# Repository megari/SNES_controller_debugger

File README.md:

SNES controller debugger
========================

This is a little project for debugging SNES controllers. The PCB design files
and the firmware source code are included.

The hardware uses an Atmel mega32u4 microcontroller.

The firmware uses the [YAAL](https://github.com/raphendyr/yaal) library and
[yaamake](https://github.com/raphendyr/yaamake). These are included as
submodules in the firmware/vendor directory.

Compilation of the firmware
---------------------------

The avr-gcc toolchain is required in order to compile the firmware. The
repositories of your distribution probably have this available.

After the toolchain has been installed:
```sh
cd firmware
```

If you haven't built yaamake yet, do so:
```sh
cd vendor/yaamake
make
cd ../..
```

Finally, build the firmware and program the board:
```sh
nano Makefile # Check that the programmer port is correct
make
make program
```

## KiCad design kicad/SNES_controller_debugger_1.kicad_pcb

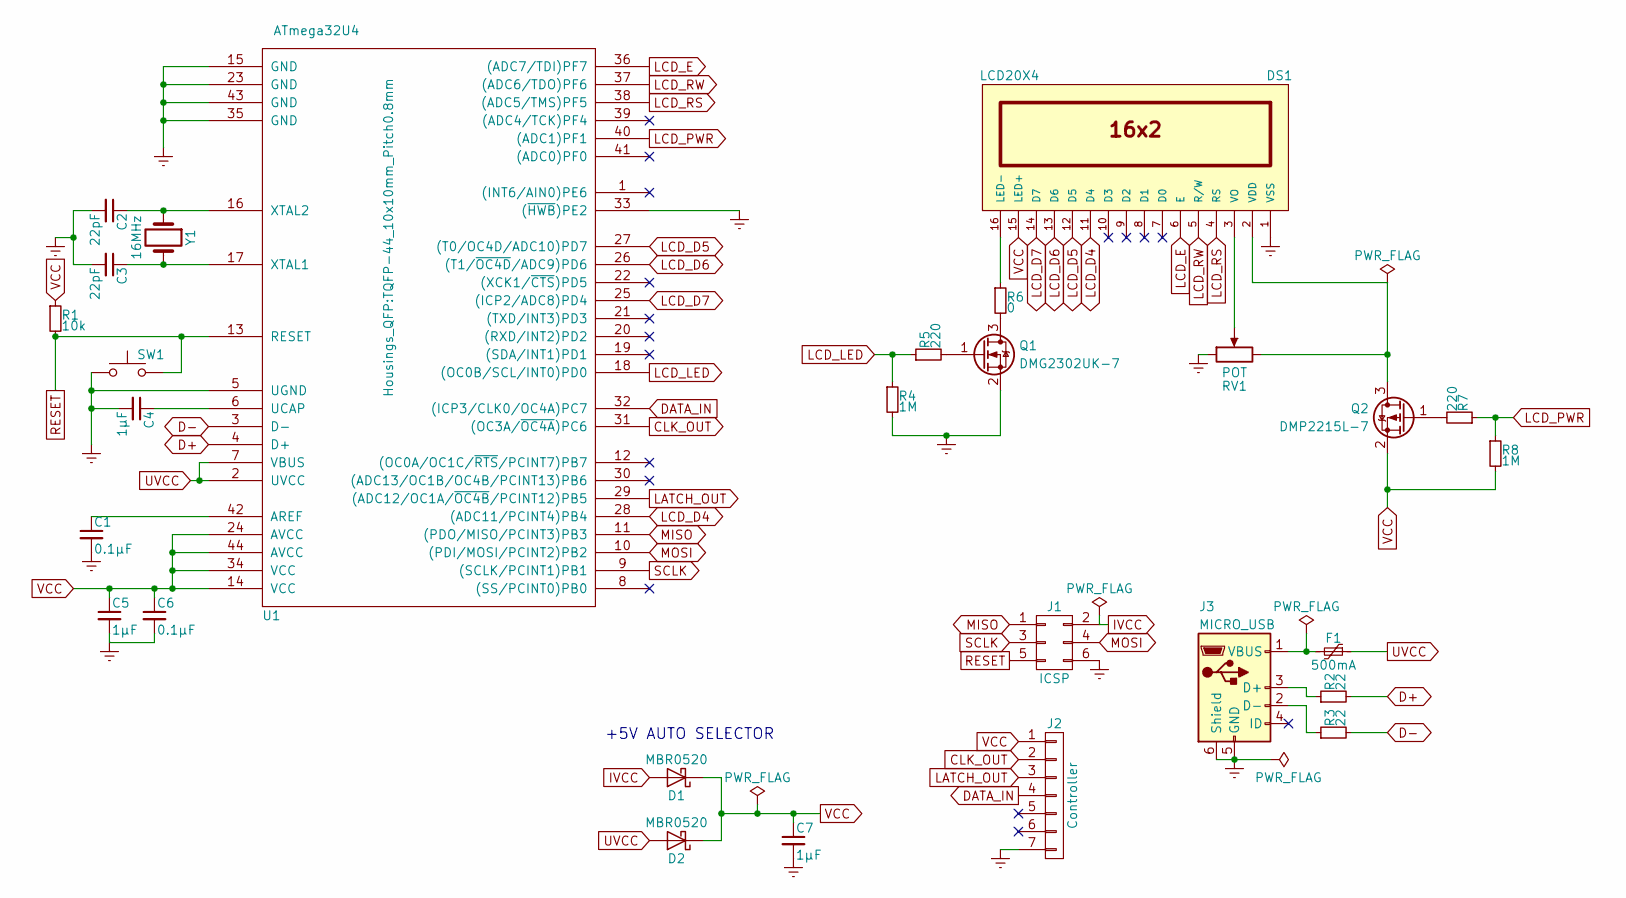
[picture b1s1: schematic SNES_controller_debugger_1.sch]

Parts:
C1, C6: 0.1µF; C_0603_HandSoldering
C2, C3: 22pF; C_0603_HandSoldering
C4, C5, C7: 1µF; C_0603_HandSoldering
D1, D2: MBR0520; D_SOD-123
DS1: LCD20X4; LCD_2004_Pitch2.54mm
F1: 500mA; R_0603_HandSoldering
J1: ICSP; Pin_Header_Straight_2x03_Pitch2.54mm
J2: Controller; SNES_controller_port
J3: MICRO_USB; Conn_USBmicro-B_Amphenol_10118194-0001LF; MPN 10118194-0001LF; Digi-Key part number 609-4618-1-ND
Q1: DMG2302UK-7; SOT-23_Handsoldering
Q2: DMP2215L-7; SOT-23_Handsoldering
R1: 10k; R_0603_HandSoldering
R2, R3: 22; R_0805_HandSoldering
R4, R8: 1M; R_0603_HandSoldering
R5, R7: 220; R_0603_HandSoldering
R6: 0; R_0603_HandSoldering
RV1: POT; Potentiometer_Trimmer_Vishay_TS53YL; MPN TS53YL103MR10; Digi-Key part number TS53YL-10KCT-ND
SW1: Reset; SW_PUSH_6mm; MPN MJTP1230; Digi-Key part number 679-2428-ND
U1: ATmega32U4; TQFP-44_10x10mm_Pitch0.8mm; MPN ATMEGA32U4-AU; Digi-Key part number ATMEGA32U4-AU-ND
Y1: 16MHz; Crystal_SMD_5032-2pin_5.0x3.2mm_HandSoldering; MPN NX5032GA-16MHZ-STD-CSK-4; Digi-Key part number 644-1187-1-ND

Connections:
CLK_OUT: J2.2, U1.31 ((OC3A/~OC4A~)PC6)
D+: R2.2, U1.4 (D+)
D-: R3.2, U1.3 (D-)
DATA_IN: J2.4, U1.32 ((ICP3/CLK0/OC4A)PC7)
Earth: C1.2, C2.2, C3.2, C4.2, C5.2, C6.2, C7.2, DS1.1 (VSS), J1.6, J2.7, J3.5 (GND), J3.6 (Shield), Q1.2 (S), R4.2, RV1.1, SW1.1, U1.5 (UGND), U1.15 (GND), U1.23 (GND), U1.33 ((~HWB~)PE2), U1.35 (GND), U1.43 (GND)
IVCC: D1.2 (A), J1.2
LATCH_OUT: J2.3, U1.29 ((ADC12/OC1A/~OC4B~/PCINT12)PB5)
LCD_D4: DS1.11 (D4), U1.28 ((ADC11/PCINT4)PB4)
LCD_D5: DS1.12 (D5), U1.27 ((T0/OC4D/ADC10)PD7)
LCD_D6: DS1.13 (D6), U1.26 ((T1/~OC4D~/ADC9)PD6)
LCD_D7: DS1.14 (D7), U1.25 ((ICP2/ADC8)PD4)
LCD_E: DS1.6 (E), U1.36 ((ADC7/TDI)PF7)
LCD_LED: R4.1, R5.1, U1.18 ((OC0B/SCL/INT0)PD0)
LCD_PWR: R7.1, R8.1, U1.40 ((ADC1)PF1)
LCD_RS: DS1.4 (RS), U1.38 ((ADC5/TMS)PF5)
LCD_RW: DS1.5 (R/W), U1.37 ((ADC6/TDO)PF6)
MISO: J1.1, U1.11 ((PDO/MISO/PCINT3)PB3)
MOSI: J1.4, U1.10 ((PDI/MOSI/PCINT2)PB2)
unnamed: C1.1, U1.42 (AREF)
unnamed: C2.1, U1.16 (XTAL2), Y1.1
unnamed: C3.1, U1.17 (XTAL1), Y1.2
unnamed: C4.1, U1.6 (UCAP)
unnamed: DS1.2 (VDD), Q2.3 (D), RV1.3
unnamed: DS1.3 (VO), RV1.2
unnamed: DS1.16 (LED-), R6.1
unnamed: F1.2, J3.1 (VBUS)
unnamed: J3.2 (D-), R3.1
unnamed: J3.3 (D+), R2.1
unnamed: Q1.1 (G), R5.2
unnamed: Q1.3 (D), R6.2
unnamed: Q2.1 (G), R7.2
RESET: J1.5, R1.2, SW1.2, U1.13 (RESET)
SCLK: J1.3, U1.9 ((SCLK/PCINT1)PB1)
UVCC: D2.2 (A), F1.1, U1.2 (UVCC), U1.7 (VBUS)
VCC: C5.1, C6.1, C7.1, D1.1 (K), D2.1 (K), DS1.15 (LED+), J2.1, Q2.2 (S), R1.1, R8.2, U1.14 (VCC), U1.24 (AVCC), U1.34 (VCC), U1.44 (AVCC)

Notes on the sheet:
+5V AUTO SELECTOR

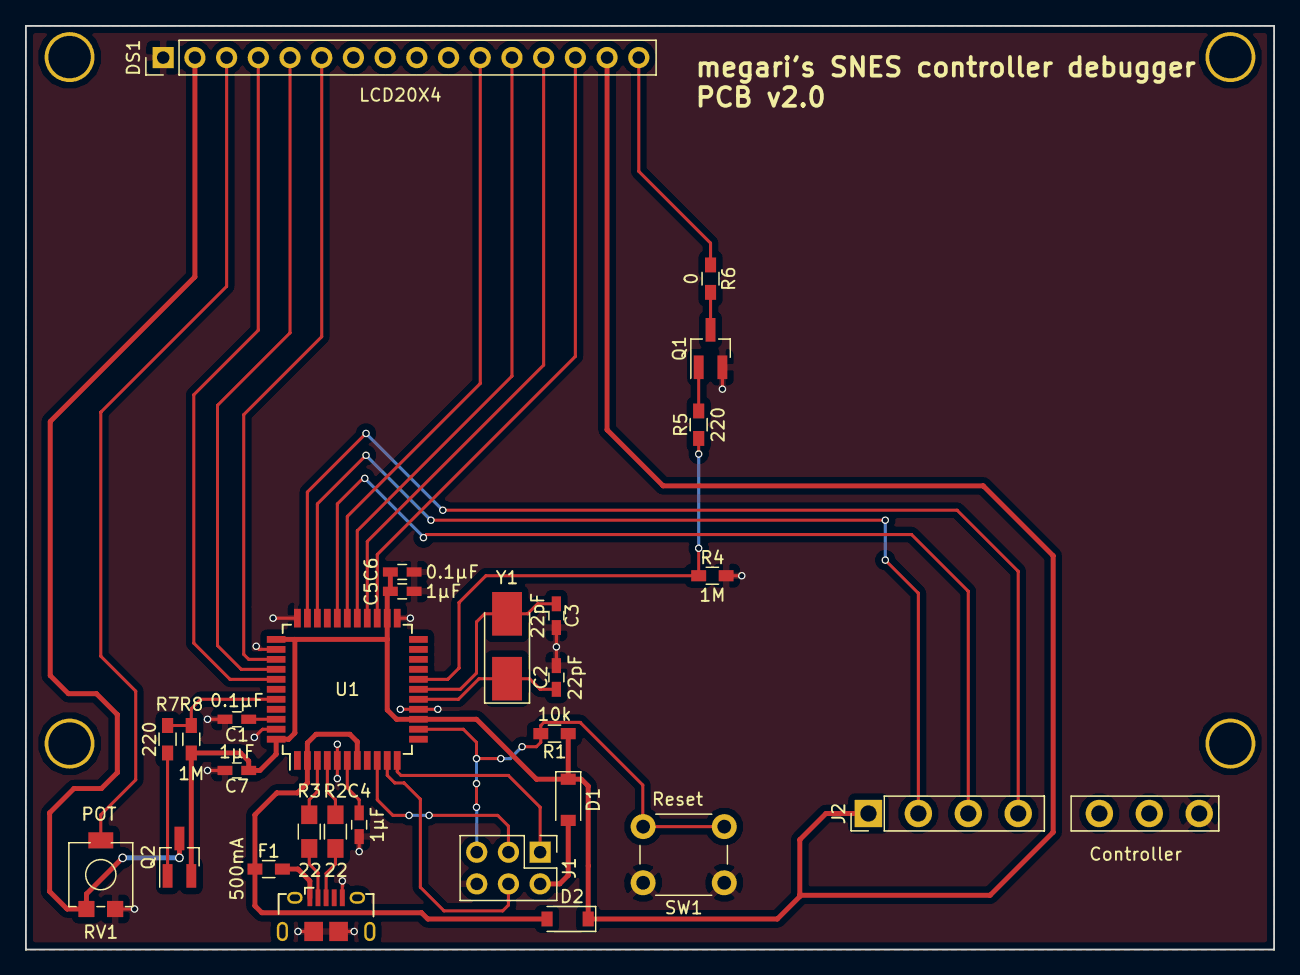
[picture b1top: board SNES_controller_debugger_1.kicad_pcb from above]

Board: 2 copper layers, 100.0 x 74.0 mm, 32 parts (0 on the bottom side), 35 nets.

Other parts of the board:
H1, H2, H3, H4: MountingHole_3.4mm

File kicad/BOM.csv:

"Id";"Designator";"Package";"Quantity";"Designation";"Supplier and ref";
1;"H4,H3,H2,H1";"MountingHole_3.4mm";4;"";;;
2;"U1";"TQFP-44_10x10mm_Pitch0.8mm";1;"ATmega32U4";;;
3;"C1,C6";"C_0603_HandSoldering";2;"0.1µF";;;
4;"C2,C3";"C_0603_HandSoldering";2;"22pF";;;
5;"C4,C5,C7";"C_0603_HandSoldering";3;"1µF";;;
6;"R1";"R_0603_HandSoldering";1;"10k";;;
7;"R2,R3";"R_0805_HandSoldering";2;"22";;;
8;"RV1";"Potentiometer_Trimmer_Vishay_TS53YL";1;"POT";;;
9;"D1,D2";"D_SOD-123";2;"MBR0520";;;
10;"F1";"R_0603_HandSoldering";1;"500mA";;;
11;"SW1";"SW_PUSH_6mm";1;"Reset";;;
12;"Y1";"Crystal_SMD_5032-2pin_5.0x3.2mm_HandSoldering";1;"16MHz";;;
13;"R4,R8";"R_0603_HandSoldering";2;"1M";;;
14;"R5,R7";"R_0603_HandSoldering";2;"220";;;
15;"R6";"R_0603_HandSoldering";1;"0";;;
16;"DS1";"LCD_2004_Pitch2.54mm";1;"LCD20X4";;;
17;"J2";"SNES_controller_port";1;"Controller";;;
18;"J1";"Pin_Header_Straight_2x03_Pitch2.54mm";1;"ICSP";;;
19;"Q1";"SOT-23_Handsoldering";1;"DMG2302UK-7";;;
20;"Q2";"SOT-23_Handsoldering";1;"DMP2215L-7";;;
21;"J3";"Conn_USBmicro-B_Amphenol_10118194-0001LF";1;"MICRO_USB";;;

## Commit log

2017-07-29 firmware: Set yaal submodule origin to upstream repostitory.
2017-08-04 pcb: Tweak USB traces, fill an area with a ground plane.
2017-08-05 pcb: Complete overhaul after getting some advice from an actual electronics engineer.
2017-08-05 pcb: Move C5 and C6 nearer to the MCU.
2017-08-06 pcb: Another complete overhaul under the supervision of Icchan^.
2017-08-07 pcb: Work on reducing the number and length of traces on the back side to make the ground plane more unified.
2017-08-08 pcb: Add Digi-Key part numbers and MPNs to some components
2017-08-10 pcb: Add hardware capability to dim the LCD backlight and to switch power to the LCD
2017-08-10 firmware: Adapt to changes in PCB version 2.0, toggle LCD off and on to re-initialize on reset
2017-08-10 firmware: Turn LCD backlight off after an idle timeout
2017-08-10 pcb: Update the BOM
2017-08-11 pcb: Generate schema PDF
2017-08-14 firmware: Update YAAL
2017-08-15 firmware: Clean up LCD power and backlight control
2017-08-15 pcb, firmware: Using an N-MOSFET to cut power to the LCD from the negative side won't work, so use a P-MOSFET on the positive side
2017-08-21 pcb: Tweak LCD screen footprint and a few traces
2017-08-25 firmware: Introduce the PowerPin class for controlling LCD power and backlight
2017-08-29 pcb: Add holes corresponding to where they are on the LCD, tweak some silkscreen texts
2017-10-09 pcb: Update gerbers, PDFs and PNGs
2017-10-09 firmware: Use upstream LCD backlight support
2017-10-12 pcb: Move all kicad files to their own separate directory
2017-12-19 firmware: Disable USB controller on startup
2017-12-19 firmware: Read 16-bit integers safely
2017-12-22 firmware: Implement PWM backlight control
2018-01-10 pcb: Fix/add some footprints
2018-03-02 firmware: Implement controller region detection
2018-03-02 firmware: Model switch WIP
2018-03-02 firmware: Fix model switch with an NES controller
2018-03-02 firmware: Move L and R a bit to better accommodate the region and model display
